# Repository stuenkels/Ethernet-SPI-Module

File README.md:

# Ethernet SPI Module based on the ENC28J60 IC
Validating my ethernet hardware design. I will use this ethernet board layout in a much larger project, just wanted to test my design and make sure it works.

This board was manufactured by PCBWay, I had it produced for free. I recomend PCBWay to anyone needing PCB or even PCBA production services. Go to pcbway.com for more details. 

## 3d View

## Finished board

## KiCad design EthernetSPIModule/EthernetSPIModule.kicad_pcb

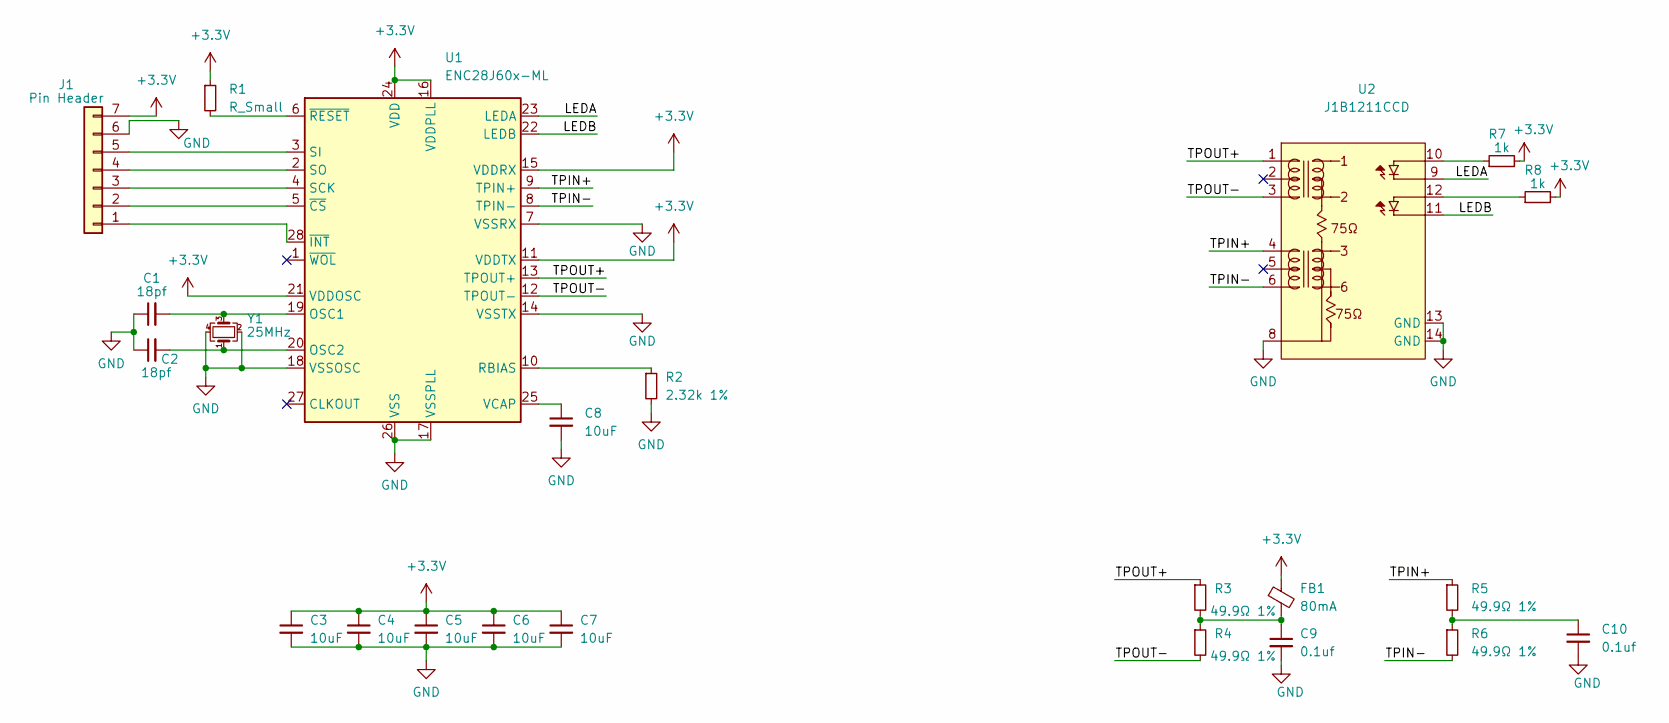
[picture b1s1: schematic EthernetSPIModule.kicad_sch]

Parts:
C1, C2: 18pf; C_0402_1005Metric
C3, C4, C5, C6, C7, C8: 10uF; C_0805_2012Metric
C9, C10: 0.1uf; C_0805_2012Metric
FB1: 80mA; R_0805_2012Metric
J1: Pin Header; PinHeader_1x07_P2.54mm_Vertical
R1: R_Small; R_0805_2012Metric
R2: 2.32k 1%; R_0805_2012Metric
R3, R4, R5, R6: 49.9Ω 1%; R_0805_2012Metric
R7, R8: 1k; R_0805_2012Metric
U1: ENC28J60x-ML; QFN-28-1EP_6x6mm_P0.65mm_EP4.25x4.25mm
U2: J1B1211CCD
Y1: 25MHz; Crystal_SMD_3225-4Pin_3.2x2.5mm

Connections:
+3.3V: C3.1, C4.1, C5.1, C6.1, C7.1, FB1.1, J1.7, R1.1, R7.2, R8.2, U1.11 (VDDTX), U1.15 (VDDRX), U1.16 (VDDPLL), U1.21 (VDDOSC), U1.24 (VDD)
/LEDA: U1.23 (LEDA), U2.9
/LEDB: U1.22 (LEDB), U2.11
/TPIN+: R5.1, U1.9 (TPIN+), U2.4
/TPIN-: R6.2, U1.8 (TPIN-), U2.6
/TPOUT+: R3.1, U1.13 (TPOUT+), U2.1
/TPOUT-: R4.2, U1.12 (TPOUT-), U2.3
unnamed: C1.2, U1.19 (OSC1), Y1.3
unnamed: C2.2, U1.20 (OSC2), Y1.1
unnamed: C8.1, U1.25 (VCAP)
unnamed: C9.1, FB1.2, R3.2, R4.1
unnamed: C10.1, R5.2, R6.1
unnamed: J1.1, U1.28 (~INT)
unnamed: J1.2, U1.5 (~CS)
unnamed: J1.3, U1.4 (SCK)
unnamed: J1.4, U1.2 (SO)
unnamed: J1.5, U1.3 (SI)
unnamed: R1.2, U1.6 (~RESET)
unnamed: R2.1, U1.10 (RBIAS)
unnamed: R7.1, U2.10
unnamed: R8.1, U2.12

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
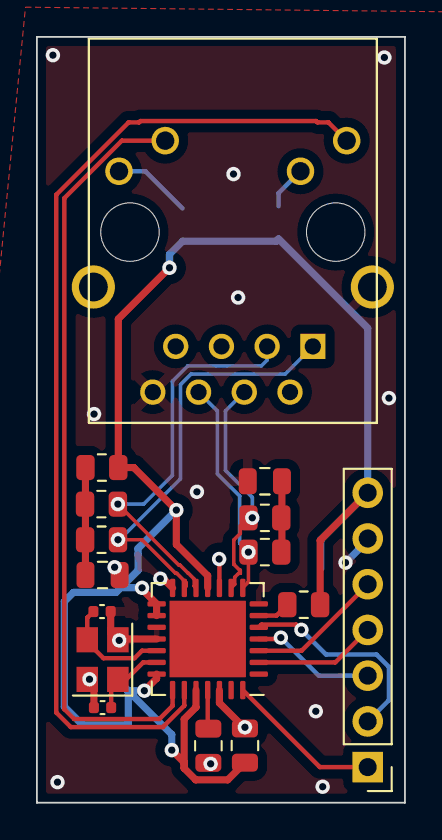
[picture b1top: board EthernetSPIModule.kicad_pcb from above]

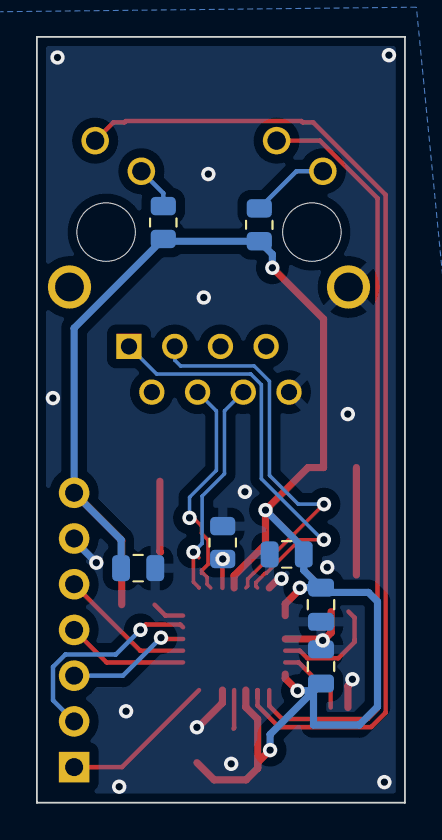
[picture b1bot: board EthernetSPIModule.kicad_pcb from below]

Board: 2 copper layers, 20.4 x 42.5 mm, 23 parts (7 on the bottom side), 22 nets.

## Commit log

2024-04-27 Added Files
2024-04-27 fixed typo
2024-04-27 PCBWay sponsorship
